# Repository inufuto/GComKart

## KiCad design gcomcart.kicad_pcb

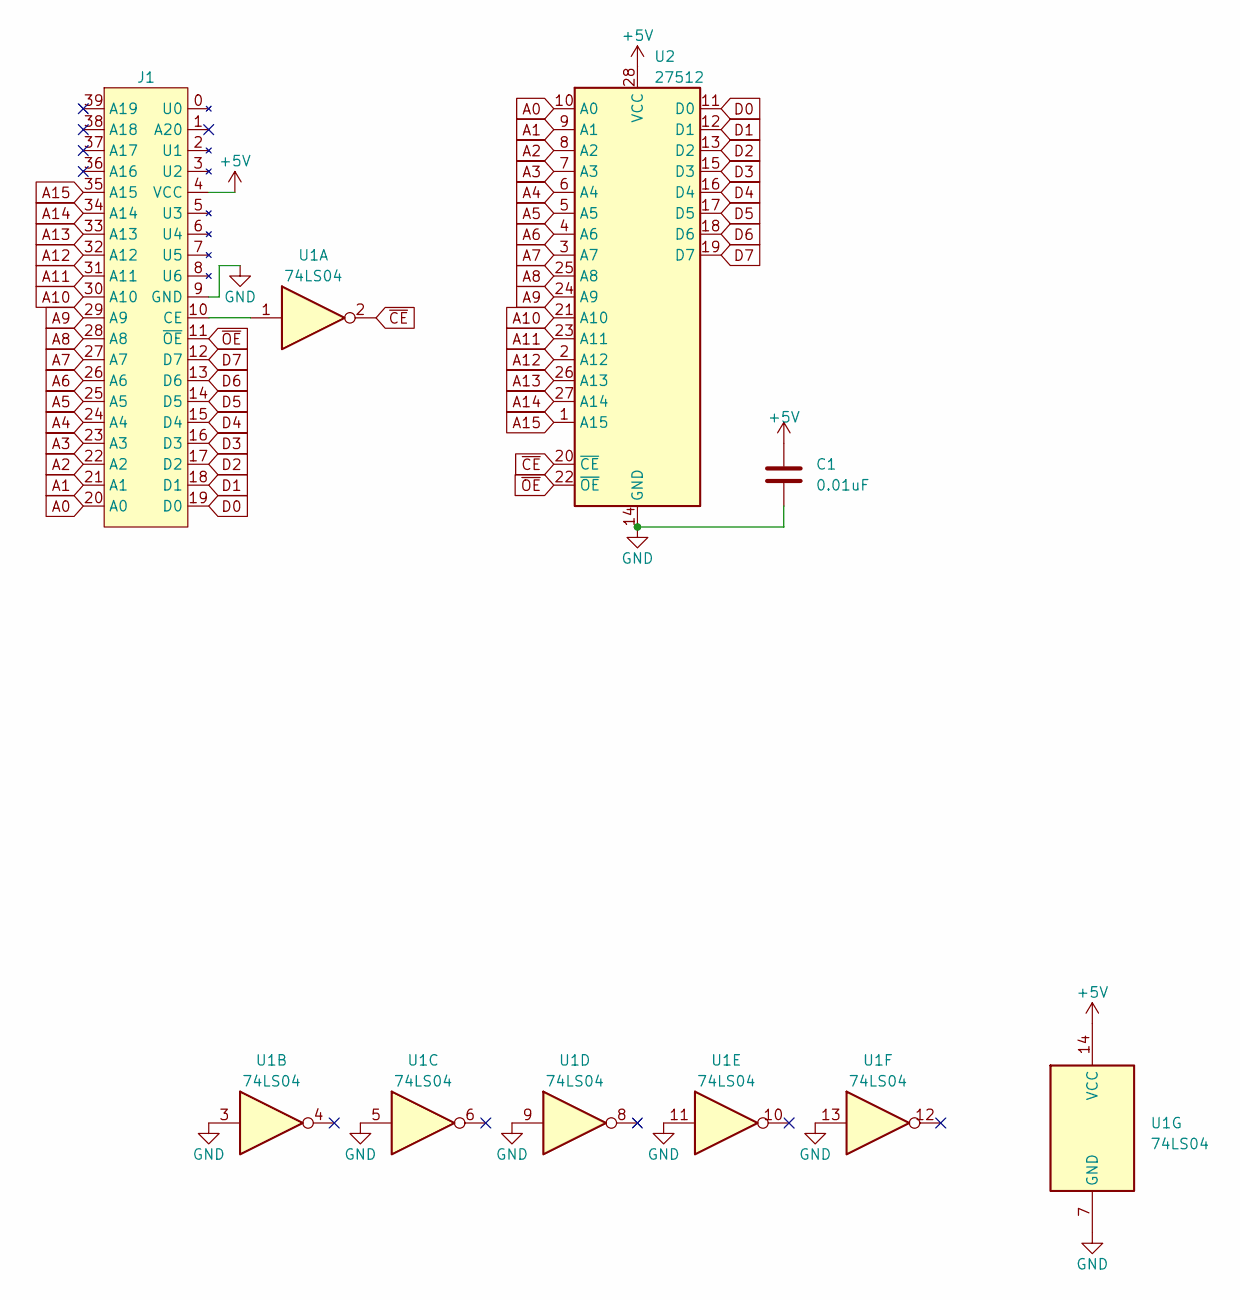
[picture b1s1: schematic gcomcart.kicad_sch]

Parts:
C1: 0.01uF; C_Disc_D5.0mm_W2.5mm_P2.50mm
J1: GameCom
U1: 74LS04; DIP-14_W7.62mm_LongPads
U2: 27512; DIP-28_W15.24mm_Socket_LongPads

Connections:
+5V: C1.1, J1.4 (VCC), U1.14 (VCC), U2.28 (VCC)
A0: J1.20 (A0), U2.10 (A0)
A1: J1.21 (A1), U2.9 (A1)
A2: J1.22 (A2), U2.8 (A2)
A3: J1.23 (A3), U2.7 (A3)
A4: J1.24 (A4), U2.6 (A4)
A5: J1.25 (A5), U2.5 (A5)
A6: J1.26 (A6), U2.4 (A6)
A7: J1.27 (A7), U2.3 (A7)
A8: J1.28 (A8), U2.25 (A8)
A9: J1.29 (A9), U2.24 (A9)
A10: J1.30 (A10), U2.21 (A10)
A11: J1.31 (A11), U2.23 (A11)
A12: J1.32 (A12), U2.2 (A12)
A13: J1.33 (A13), U2.26 (A13)
A14: J1.34 (A14), U2.27 (A14)
A15: J1.35 (A15), U2.1 (A15)
D0: J1.19 (D0), U2.11 (D0)
D1: J1.18 (D1), U2.12 (D1)
D2: J1.17 (D2), U2.13 (D2)
D3: J1.16 (D3), U2.15 (D3)
D4: J1.15 (D4), U2.16 (D4)
D5: J1.14 (D5), U2.17 (D5)
D6: J1.13 (D6), U2.18 (D6)
D7: J1.12 (D7), U2.19 (D7)
GND: C1.2, J1.9 (GND), U1.3, U1.5, U1.7 (GND), U1.9, U1.11, U1.13, U2.14 (GND)
unnamed: J1.10 (CE), U1.1
~CE: U1.2, U2.20 (~CE)
~OE: J1.11 (~OE), U2.22 (~OE)

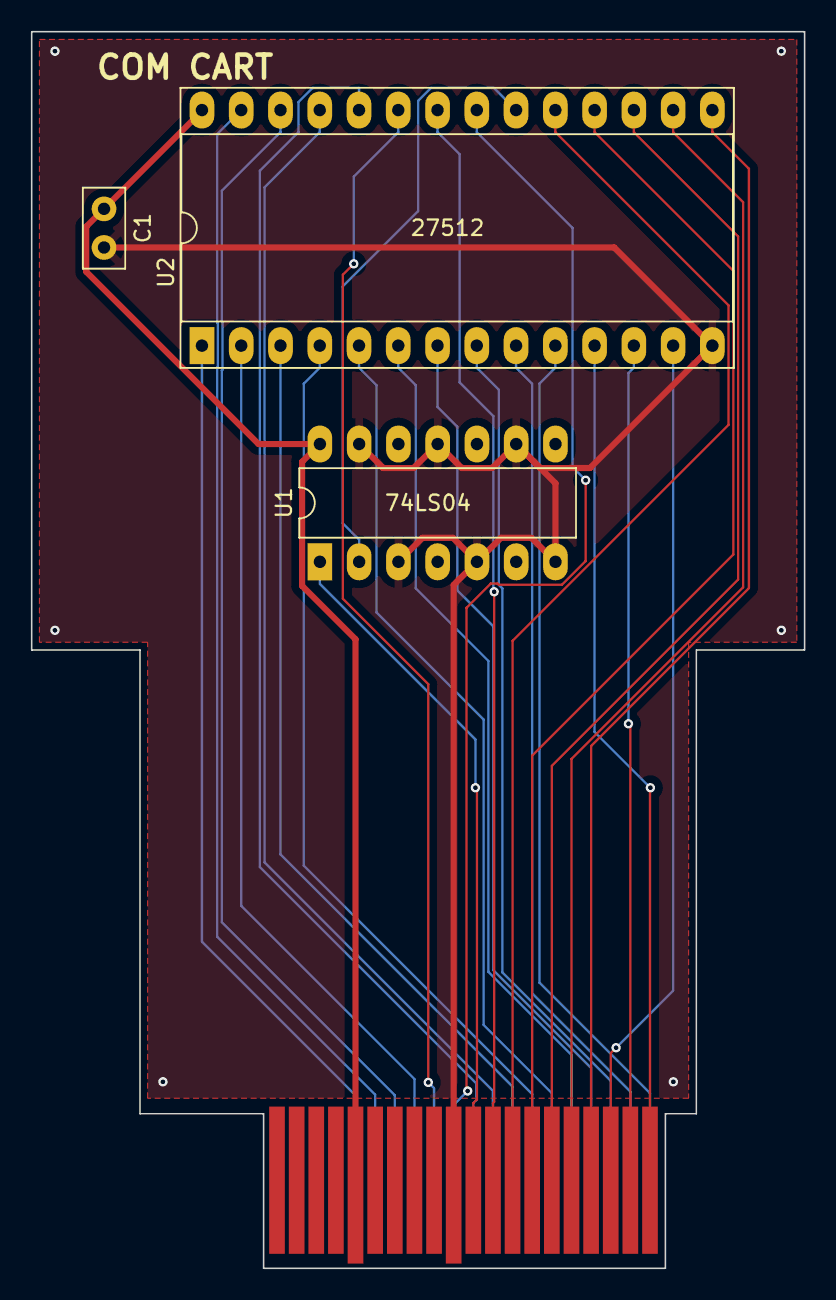
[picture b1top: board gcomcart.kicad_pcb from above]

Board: 2 copper layers, 50.0 x 80.0 mm, 4 parts (0 on the bottom side), 29 nets.
